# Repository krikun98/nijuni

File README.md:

# Nijuni

The Nijuni (formerly known as the RT-22) is a 44-key split keyboard inspired by the [Jian](https://github.com/KGOH/Jian-Info) (stagger, pinky and controller footprint) and the 
[Jorne](https://github.com/joric/jorne) (thumb cluster and wiring).

It was originally conceived by [DwarZ](https://t.me/rafworksintl), however, V0.1 had a screw placement issue that restricted it to Kailh BOX-style switches.
V0.2 is trouble-free, and prototypes have already been tested.

The image above depicts V0.1, and power switch hacks are no longer necessary.
It also links to a typing video.

## Features

* Wireless focus - battery footprint, power switches and no LEDs in sight
* Uses Jorne firmware - so QMK and ZMK support
* MX or Alps soldered or MX hotswap support in a single reversible PCB
* 6 column version also available for 100x150 PCB promos.

## Download

You can download Gerber and DXF files in the [releases section](https://github.com/krikun98/nijuni/releases).
More images are also in Actions builds.

## Instructions

### Firmware

The Nijuni is fully pin-compatible with the Jorne (and the 6 column version is compatible with the Corne), so both ZMK and QMK support it already.

### BOM/Build instructions

The Nijuni is not that different to a regular Jorne, so please refer to [Joric's wonderful wiki](https://github.com/joric/jorne/wiki) for all the instructions.

The only major difference is the controller footprint.
The Jian has a [build guide](https://telegra.ph/Gajd-po-sborke-Jian-12-08) in Russian, but the pictures should be easy enough to follow along with.

An older version of the controller footprint had a problem: the solder could flow through and short something on top.
This should not happen anymore, as the holes were shrunk down to accept spring pin headers, but if it still does - please file an issue.

## Links

### Version 0.2

Full 7-column PCB

[IBOM](https://htmlpreview.github.io/?https://github.com/krikun98/nijuni/blob/main/pcb/pinky/bom/ibom.html)

[gerbers](../../releases/latest/download/pcb_pinky_gerbers.zip)

front|back
--|--
|

6-column version

[IBOM](https://htmlpreview.github.io/?https://github.com/krikun98/nijuni/blob/main/pcb/6col/bom/ibom.html)

[gerbers](../../releases/latest/download/pcb_6col_gerbers.zip)

front|back
--|--
|

[Case gerbers](../../releases/latest/download/gerber_case_files.zip)

[Case files for laser cutting](../../releases/latest/download/laser_case_files.zip)

All the case files labeled "plastic" have the switch holes adjusted(0.25 mm. smaller in both dimensions).
If your laser cutter has different tolerances - adjust them and re-run the build script.

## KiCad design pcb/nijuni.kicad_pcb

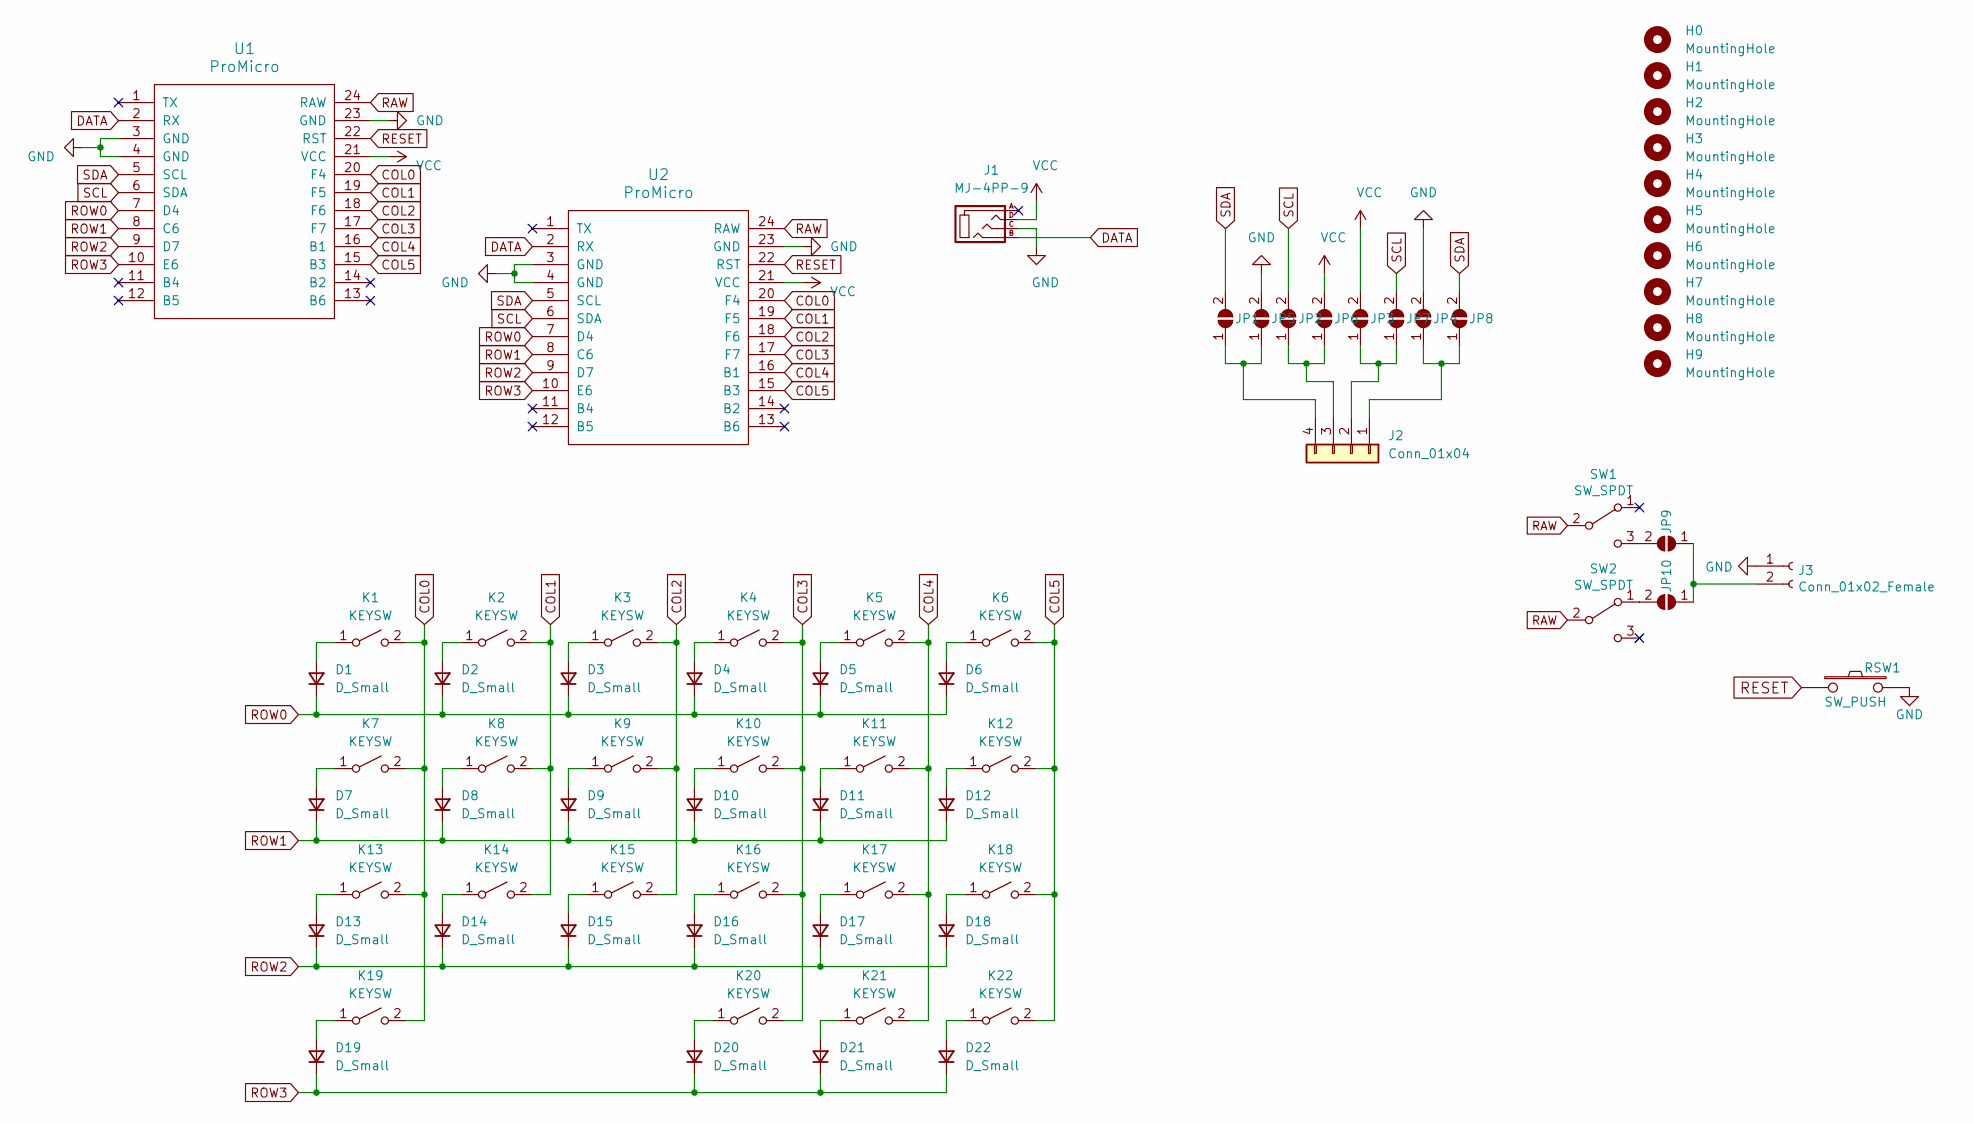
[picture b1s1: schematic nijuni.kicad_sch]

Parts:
D1, D2, D3, D4, D5, D6, D7, D8, D9, D10, D11, D12, D13, D14, D15, D16, D17, D18, D19, D20, D21, D22: D_Small; D3_SMD
H0, H1, H2, H3, H4, H5, H6, H7: MountingHole; M2-MountingHole-Standoff
H8, H9: MountingHole; M2-ClearanceHole
J1: MJ-4PP-9
J2: Conn_01x04; OLED_DISPLAY_128x32px_0.91in
J3: Conn_01x02_Female; Battery_TH
JP1, JP2, JP3, JP4, JP5, JP6, JP7, JP8, JP9, JP10: SolderJumper_2_Open; SolderJumper-2_P1.3mm_Open_RoundedPad1.0x1.5mm
K1, K2, K3, K4, K5, K6, K7, K8, K9, K10, K11, K12, K13, K14, K15, K16, K17, K18, K19, K20, K21: KEYSW; MX-Alps-HS-1U-REV
K22: KEYSW; MX-Alps-HS-1.5U-REV
RSW1: SW_PUSH; ResetSW
SW1, SW2: SW_SPDT; SW_SPDT+H-MSK12C01_hor(7pin_SMD)
U1: ProMicro; ProMicro_Flipped_v2_A
U2: ProMicro; ProMicro_Flipped_v2_B

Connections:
COL0: K1.2 (B), K7.2 (B), K13.2 (B), K19.2 (B), U1.20 (F4), U2.20 (F4)
COL1: K2.2 (B), K8.2 (B), K14.2 (B), U1.19 (F5), U2.19 (F5)
COL2: K3.2 (B), K9.2 (B), K15.2 (B), U1.18 (F6), U2.18 (F6)
COL3: K4.2 (B), K10.2 (B), K16.2 (B), K20.2 (B), U1.17 (F7), U2.17 (F7)
COL4: K5.2 (B), K11.2 (B), K17.2 (B), K21.2 (B), U1.16 (B1), U2.16 (B1)
COL5: K6.2 (B), K12.2 (B), K18.2 (B), K22.2 (B), U1.15 (B3), U2.15 (B3)
DATA: J1.B, U1.2 (RX), U2.2 (RX)
GND: J1.C, J3.1, JP4.2 (B), JP5.2 (B), RSW1.2, U1.3 (GND), U1.4 (GND), U1.23 (GND), U2.3 (GND), U2.4 (GND), U2.23 (GND)
unnamed: D1.2 (A), K1.1 (A)
unnamed: D2.2 (A), K2.1 (A)
unnamed: D3.2 (A), K3.1 (A)
unnamed: D4.2 (A), K4.1 (A)
unnamed: D5.2 (A), K5.1 (A)
unnamed: D6.2 (A), K6.1 (A)
unnamed: D7.2 (A), K7.1 (A)
unnamed: D8.2 (A), K8.1 (A)
unnamed: D9.2 (A), K9.1 (A)
unnamed: D10.2 (A), K10.1 (A)
unnamed: D11.2 (A), K11.1 (A)
unnamed: D12.2 (A), K12.1 (A)
unnamed: D13.2 (A), K13.1 (A)
unnamed: D14.2 (A), K14.1 (A)
unnamed: D15.2 (A), K15.1 (A)
unnamed: D16.2 (A), K16.1 (A)
unnamed: D17.2 (A), K17.1 (A)
unnamed: D18.2 (A), K18.1 (A)
unnamed: D19.2 (A), K19.1 (A)
unnamed: D20.2 (A), K20.1 (A)
unnamed: D21.2 (A), K21.1 (A)
unnamed: D22.2 (A), K22.1 (A)
unnamed: J2.1, JP4.1 (A), JP8.1 (A)
unnamed: J2.2, JP3.1 (A), JP7.1 (A)
unnamed: J2.3, JP2.1 (A), JP6.1 (A)
unnamed: J2.4, JP1.1 (A), JP5.1 (A)
unnamed: J3.2, JP9.1 (A), JP10.1 (A)
unnamed: JP9.2 (B), SW1.3 (C)
unnamed: JP10.2 (B), SW2.1 (A)
RAW: SW1.2 (B), SW2.2 (B), U1.24 (RAW), U2.24 (RAW)
RESET: RSW1.1, U1.22 (RST), U2.22 (RST)
ROW0: D1.1 (K), D2.1 (K), D3.1 (K), D4.1 (K), D5.1 (K), D6.1 (K), U1.7 (D4), U2.7 (D4)
ROW1: D7.1 (K), D8.1 (K), D9.1 (K), D10.1 (K), D11.1 (K), D12.1 (K), U1.8 (C6), U2.8 (C6)
ROW2: D13.1 (K), D14.1 (K), D15.1 (K), D16.1 (K), D17.1 (K), D18.1 (K), U1.9 (D7), U2.9 (D7)
ROW3: D19.1 (K), D20.1 (K), D21.1 (K), D22.1 (K), U1.10 (E6), U2.10 (E6)
SCL: JP2.2 (B), JP7.2 (B), U1.6 (SDA), U2.6 (SDA)
SDA: JP1.2 (B), JP8.2 (B), U1.5 (SCL), U2.5 (SCL)
VCC: J1.D, JP3.2 (B), JP6.2 (B), U1.21 (VCC), U2.21 (VCC)

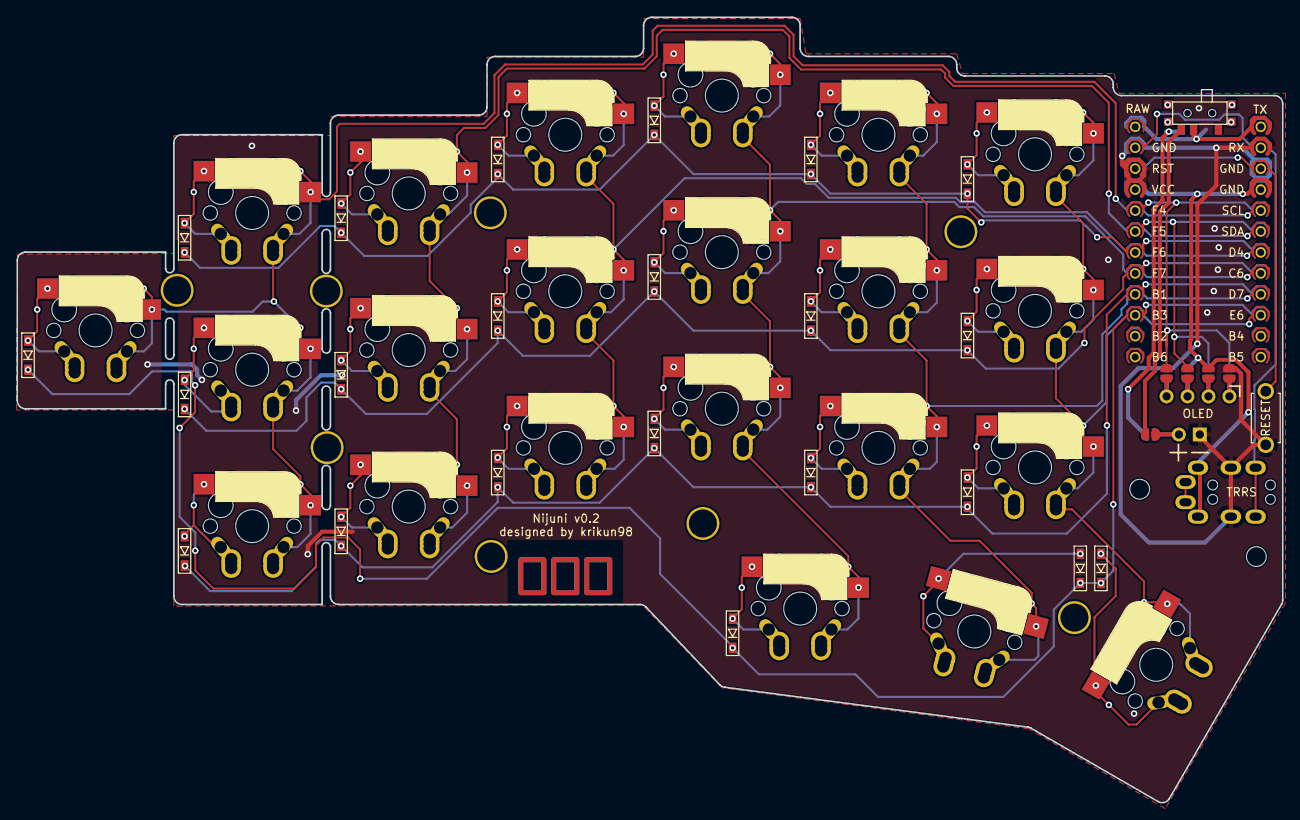
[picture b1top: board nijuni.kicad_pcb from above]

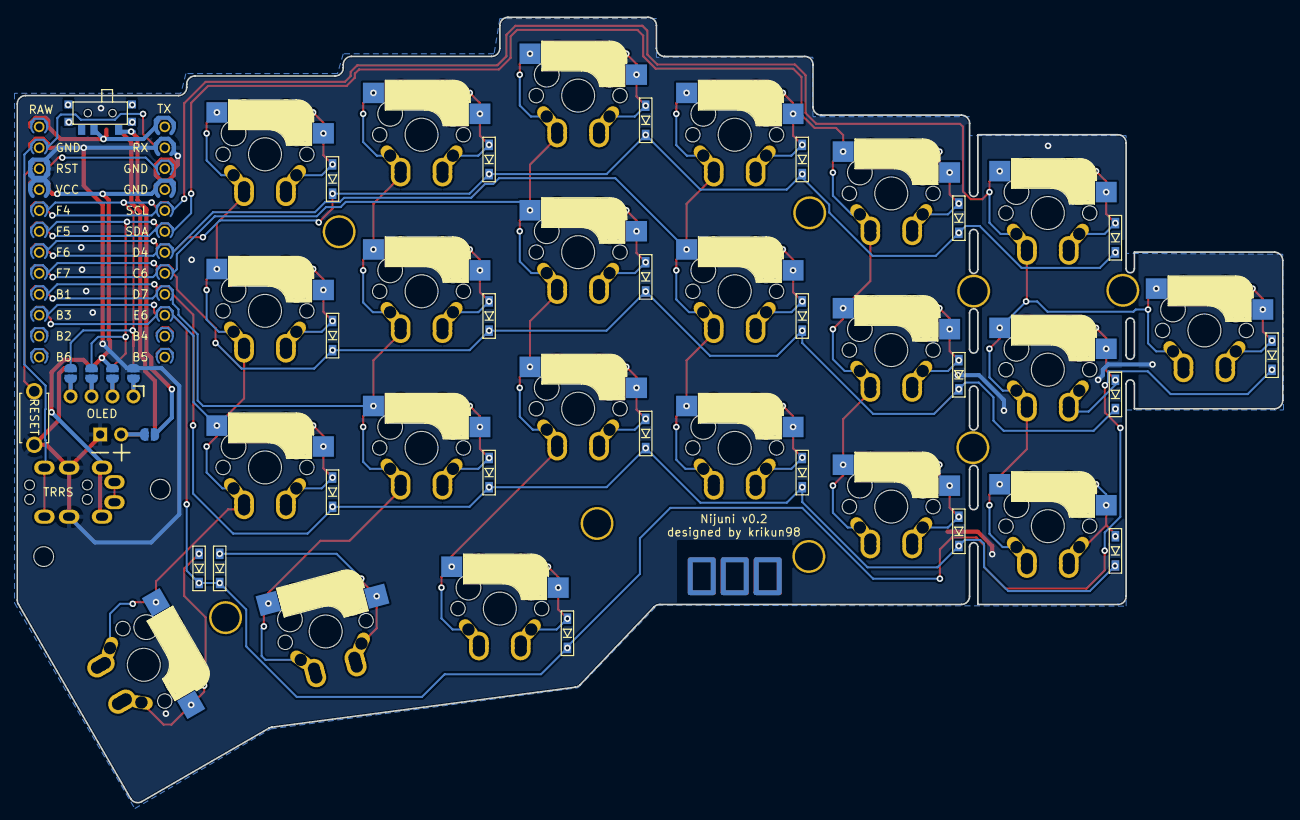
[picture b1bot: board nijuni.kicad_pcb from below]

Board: 2 copper layers, 153.6 x 95.3 mm, 72 parts (7 on the bottom side), 46 nets.

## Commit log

2021-12-10 Nijuni V0.2
2022-01-07 Cosmetic adjustments
2022-01-07 Pinky PCB
2022-01-07 6 column variant
2022-01-07 Bottom adjustments
2022-01-07 Plate adjustments
2022-01-08 Back to solid fills
2022-01-08 Typo
2022-01-08 Artifact naming consistency
2022-01-08 Artifact path fix
2022-01-08 Artifact path fix 2
2022-01-08 Add readme
2022-01-08 Added pictures
2022-01-08 Change image colours
2022-01-08 Remove hand-built artifacts
2022-01-08 Add video link
2022-01-08 Added proper footprint dependencies
2022-01-08 Library tables
2022-01-08 Update README.md
    Fixed the link in Download section as it was previously pointing out to Jorian.
2022-01-08 Ground fill fix
2022-01-09 Bottom DXF fix, also added solid plate/bottom gerbers
2022-01-09 Added fr4 6col plate
2022-01-11 Updated laser cutting files
2022-02-14 6col IBOM link fix
2022-05-31 fixed kikit version
2023-10-11 KiKit 1.3.0 build script edits
2023-10-11 Update actions
    Update version dependencies and formats
